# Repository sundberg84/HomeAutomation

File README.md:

# Homeautomation Backup! 
My homeautomation stuff backup place :)

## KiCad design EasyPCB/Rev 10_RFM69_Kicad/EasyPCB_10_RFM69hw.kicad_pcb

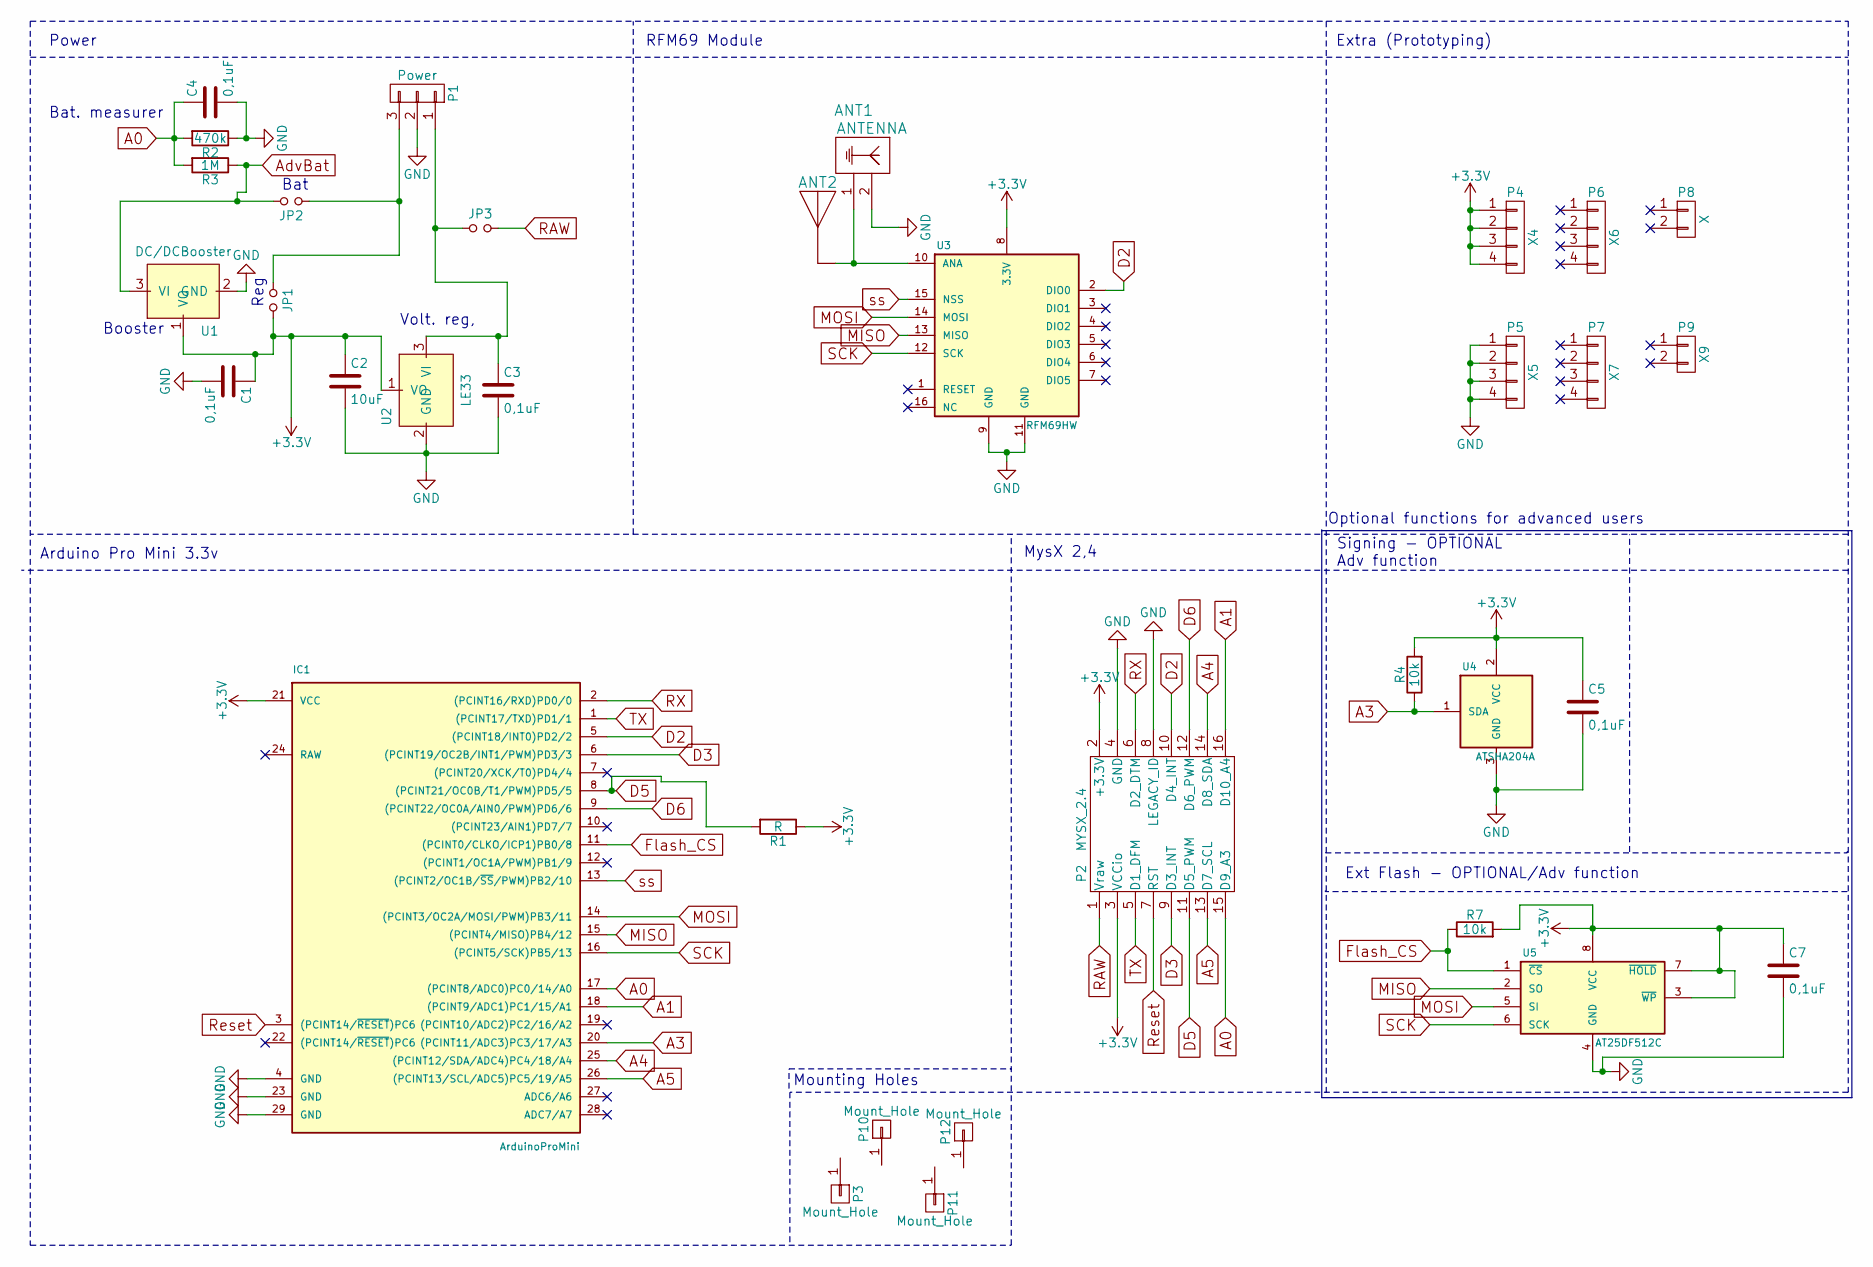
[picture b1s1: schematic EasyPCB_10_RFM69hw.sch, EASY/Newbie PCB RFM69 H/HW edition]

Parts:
ANT1: ANTENNA; SMA_EDGE
ANT2: ANTENNA; Pin_Header_Straight_1x01_Pitch2.54mm
C1, C3, C4: 0,1uF; CP_Radial_D5.0mm_P2.50mm
C2: 10uF; CP_Radial_D5.0mm_P2.50mm
C5, C7: 0,1uF; C_0805_HandSoldering
IC1: ArduinoProMini; pro_mini
JP1: REG; Pin_Header_Straight_1x02_Pitch2.54mm
JP2: BAT; Pin_Header_Straight_1x02_Pitch2.54mm
JP3: RAW; Pin_Header_Straight_1x02_Pitch2.54mm
P1: Power; 3_block_Screw_Terminal
P2: MYSX_2.4
P3, P10, P11, P12: Mount_Hole; MountingHole_2.5mm
P4: X4; Pin_Header_Straight_1x04_Pitch2.54mm
P5: X5; Pin_Header_Straight_1x04_Pitch2.54mm
P6: X6; Pin_Header_Straight_1x04_Pitch2.54mm
P7: X7; Pin_Header_Straight_1x04_Pitch2.54mm
P8: X; Pin_Header_Straight_1x02_Pitch2.54mm
P9: X9; Pin_Header_Straight_1x02_Pitch2.54mm
R1: R; R_Axial_DIN0207_L6.3mm_D2.5mm_P10.16mm_Horizontal
R2: 470k; R_Axial_DIN0207_L6.3mm_D2.5mm_P7.62mm_Horizontal
R3: 1M; R_Axial_DIN0207_L6.3mm_D2.5mm_P7.62mm_Horizontal
R4, R7: 10k; R_0805_HandSoldering
U1: DC/DCBooster; Pin_Header_Straight_1x03_Pitch2.54mm
U2: LE33; TO-92_LE33_Andreas
U3: RFM69HW; RFM69HW_SMD_ThroughHole_Handsoldering
U4: ATSHA204A; SOT-23_Handsoldering
U5: AT25DF512C; SOIC-8_3.9x4.9mm_Pitch1.27mm

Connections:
+3V3: C1.1, C2.1, C5.1, C7.1, IC1.21 (VCC), JP1.2, P2.2 (+3.3V), P2.3 (VCCio), P4.1, P4.2, P4.3, P4.4, R1.1, R4.2, R7.2, U1.1 (VO), U2.1 (VO), U3.8 (3.3V), U4.2 (VCC), U5.3 (~WP), U5.7 (~HOLD), U5.8 (VCC)
A0: C4.1, IC1.17 ((PCINT8/ADC0)PC0/14/A0), P2.15 (D9_A3), R2.2, R3.2
A1: IC1.18 ((PCINT9/ADC1)PC1/15/A1), P2.16 (D10_A4)
A3: IC1.20 ((PCINT11/ADC3)PC3/17/A3), R4.1, U4.1 (SDA)
A4: IC1.25 ((PCINT12/SDA/ADC4)PC4/18/A4), P2.14 (D8_SDA)
A5: IC1.26 ((PCINT13/SCL/ADC5)PC5/19/A5), P2.13 (D7_SCL)
AdvBat: JP2.2, R3.1, U1.3 (VI)
D2: IC1.5 ((PCINT18/INT0)PD2/2), P2.10 (D4_INT), U3.2 (DIO0)
D3: IC1.6 ((PCINT19/OC2B/INT1/PWM)PD3/3), P2.9 (D3_INT)
D5: IC1.8 ((PCINT21/OC0B/T1/PWM)PD5/5), P2.11 (D5_PWM), R1.2
D6: IC1.9 ((PCINT22/OC0A/AIN0/PWM)PD6/6), P2.12 (D6_PWM)
Flash_CS: IC1.11 ((PCINT0/CLKO/ICP1)PB0/8), R7.1, U5.1 (~CS)
GND: ANT1.2, C1.2, C2.2, C3.2, C4.2, C5.2, C7.2, IC1.4 (GND), IC1.23 (GND), IC1.29 (GND), P1.2, P2.4 (GND), P2.8 (LEGACY_ID), P5.1, P5.2, P5.3, P5.4, R2.1, U1.2 (GND), U2.2 (GND), U3.9 (GND), U3.11 (GND), U4.3 (GND), U5.4 (GND)
MISO: IC1.15 ((PCINT4/MISO)PB4/12), U3.13 (MISO), U5.2 (SO)
MOSI: IC1.14 ((PCINT3/OC2A/MOSI/PWM)PB3/11), U3.14 (MOSI), U5.5 (SI)
unnamed: ANT1.1, ANT2.1, U3.10 (ANA)
unnamed: C3.1, JP3.1, P1.1, U2.3 (VI)
unnamed: JP1.1, JP2.1, P1.3
RAW: JP3.2, P2.1 (Vraw)
RX: IC1.2 ((PCINT16/RXD)PD0/0), P2.6 (D2_DTM)
Reset: IC1.3 ((PCINT14/~RESET~)PC6), P2.7 (RST)
SCK: IC1.16 ((PCINT5/SCK)PB5/13), U3.12 (SCK), U5.6 (SCK)
TX: IC1.1 ((PCINT17/TXD)PD1/1), P2.5 (D1_DFM)
ss: IC1.13 ((PCINT2/OC1B/~SS~/PWM)PB2/10), U3.15 (NSS)

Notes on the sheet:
Reg
Bat
Power
Bat. measurer
Booster
Volt. reg,
MysX 2,4
Extra (Prototyping)
RFM69 Module
Arduino Pro Mini 3.3v
Signing - OPTIONAL Adv function
Ext Flash - OPTIONAL/Adv function
Optional functions for advanced users
Mounting Holes

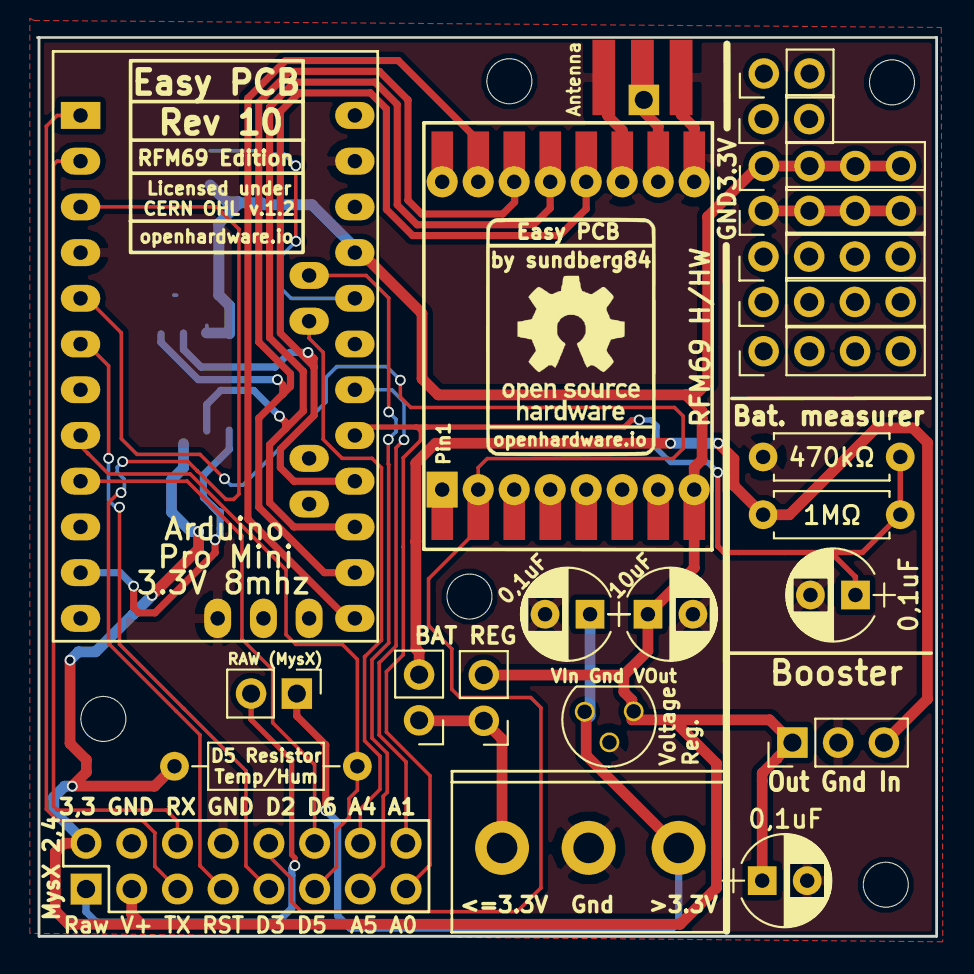
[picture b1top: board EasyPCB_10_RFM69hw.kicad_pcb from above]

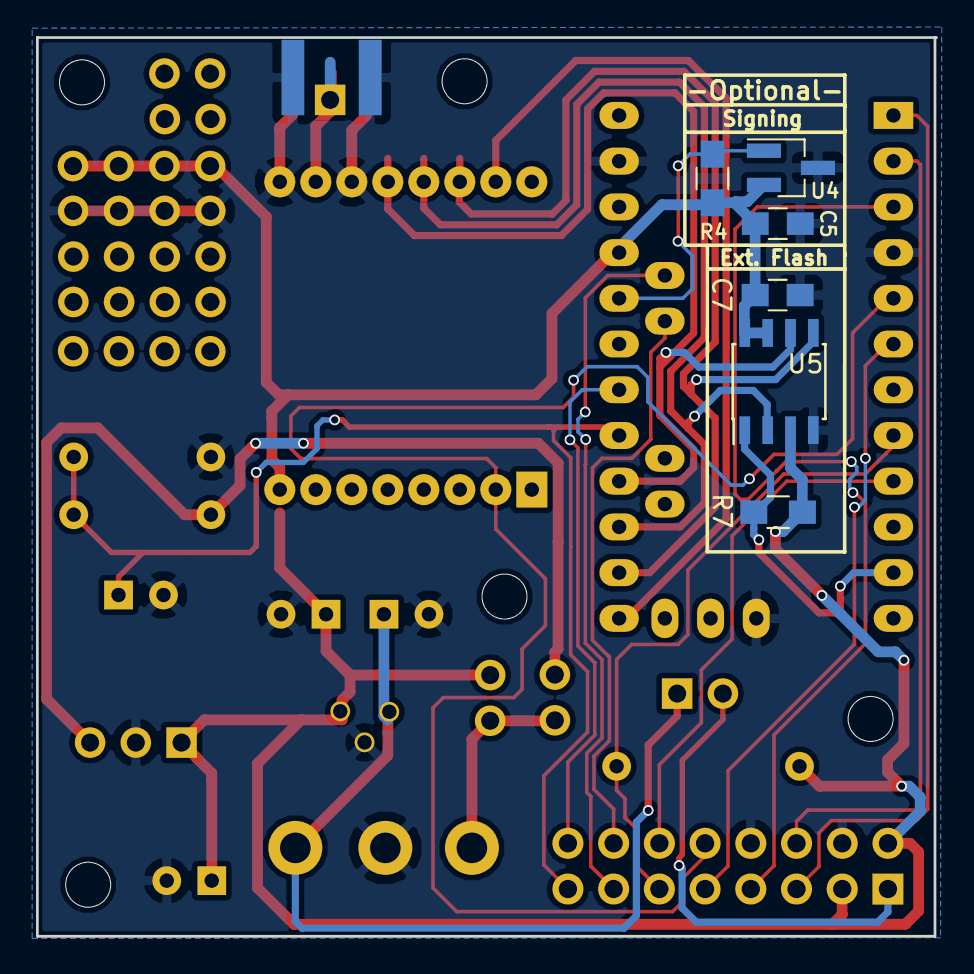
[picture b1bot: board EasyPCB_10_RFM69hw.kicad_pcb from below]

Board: 2 copper layers, 50.0 x 49.9 mm, 36 parts (6 on the bottom side), 24 nets.

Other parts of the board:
P3#2, P3#3: Mount_Hole; MountingHole_2.5mm
P7#2: X7; Pin_Header_Straight_1x04_Pitch2.54mm

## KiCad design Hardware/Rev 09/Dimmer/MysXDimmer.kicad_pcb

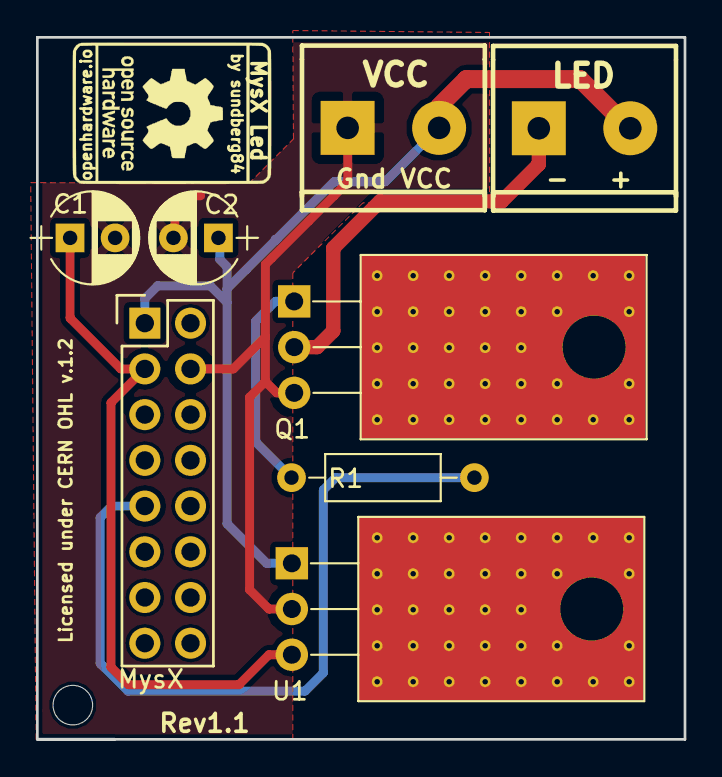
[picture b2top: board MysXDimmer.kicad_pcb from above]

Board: 2 copper layers, 36.0 x 39.0 mm, 8 parts (0 on the bottom side), 6 nets.

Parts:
C1, C2: CP1; CP_Radial_D5.0mm_P2.50mm
LED: CONN_LED; mors_2p
MysX: CONN_02X06; MYSX_2.4
Q1: IRLZ44; TO-220-3_w_heatsink
R1: R; R_Axial_DIN0207_L6.3mm_D2.5mm_P10.16mm_Horizontal
U1: LM2940/LM2940C; TO-220-3_w_heatsink
VCC: CONN_12vDC; mors_2p

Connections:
12v: C2.1, LED.2, MysX.1, U1.1, VCC.2
12vLed: LED.1, Q1.2
+5V: C1.1, MysX.3, U1.3
GND: C1.2, C2.2, MysX.4, Q1.2, Q1.3, Q1.4, U1.2, VCC.1
LED1: MysX.9, R1.2
unnamed: Q1.1, R1.1

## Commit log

2016-09-13 :boom::camel: Added .gitattributes & .gitignore files
2016-09-13 Nya filer
    Nya sketcher
2017-01-10 Energimeter
2017-01-17 NorrHum
2017-02-05 Somethings
2017-02-05 en till
2017-02-06 Removed resend 0 and trigger=!oldtrigger
2017-02-20 Div från kallaren
2017-02-21 Create FirstCommunication1245
2017-02-21 Change format txt
2017-02-21 SerialTest för gw
2017-03-01 Create ComNibeHardwareSerial
2017-04-21 UV Changes
    UV CHanges
2017-08-12 New stuff
2017-08-31 Create Log24hRFM
2017-08-31 Rename Log24hRFM to Log24hRFM.txt
2017-08-31 Rename Log24hRFM.txt to Logs/Log24hRFM.txt
2017-08-31 Rename Log24hNRF.txt to Log24h_NRF_REG.txt
2017-08-31 Rename Log24hRFM.txt to Log24hRFM_REG.txt
2017-08-31 Rename Log24hRFM_REG.txt to Log24h_RFM_REG.txt
2017-08-31 Create LOG24h_RFM_BAT
2017-09-16 New files!
2017-10-25 Some new Files and updates.
2017-11-23 New structure
2017-11-23 Openlogger added to project.
2018-01-07 Update BatteryMeasurer.ino
    If debug defined
2018-02-17 Added MysX Template
2018-02-17 Image
    Image
2018-02-17 Added mounting holes
    M Hole
2018-02-17 Image
2018-03-07 Nodes
2018-03-07 RadioTester
2018-03-08 New File
2018-03-16 TimeAwareSensor Mys 2
2018-04-19 MysXDimmer
2018-06-05 EasyPCB Revision 10 update
    EasyPCB Revision 10 update
2018-06-05 Uploaded Rev 10 Gerber
2018-06-05 Rename MysX template EasyPCB/MysX Template EasyPCB Rev10-B.Cu.gbr to MysX template EasyPCB/Gerber/MysX Template EasyPCB Rev10-B.Cu.gbr
2018-06-05 Rename MysX template EasyPCB/MysX Template EasyPCB Rev10-B.Mask.gbr to MysX template EasyPCB/Gerber/MysX Template EasyPCB Rev10-B.Mask.gbr
2018-06-05 Rename MysX template EasyPCB/MysX Template EasyPCB Rev10-B.SilkS.gbr to MysX template EasyPCB/Gerber/MysX Template EasyPCB Rev10-B.SilkS.gbr
2018-06-05 Rename MysX template EasyPCB/MysX Template EasyPCB Rev10-Edge.Cuts.gbr to MysX template EasyPCB/Gerber/MysX Template EasyPCB Rev10-Edge.Cuts.gbr
2018-06-05 Rename MysX template EasyPCB/MysX Template EasyPCB Rev10-F.Cu.gbr to MysX template EasyPCB/Gerber/MysX Template EasyPCB Rev10-F.Cu.gbr
2018-06-05 Rename MysX template EasyPCB/MysX Template EasyPCB Rev10-F.Mask.gbr to MysX template EasyPCB/Gerber/MysX Template EasyPCB Rev10-F.Mask.gbr
2018-06-05 Rename MysX template EasyPCB/MysX Template EasyPCB Rev10-F.SilkS.gbr to MysX template EasyPCB/Gerber/MysX Template EasyPCB Rev10-F.SilkS.gbr
2018-06-05 Rename MysX template EasyPCB/MysX Template EasyPCB Rev10-NPTH.drl to MysX template EasyPCB/Gerber/MysX Template EasyPCB Rev10-NPTH.drl
2018-06-05 Rename MysX template EasyPCB/MysX Template EasyPCB Rev10.drl to MysX template EasyPCB/Gerber/MysX Template EasyPCB Rev10.drl
2018-06-06 Från Källardatorn
2019-04-07 Update DoorBellDec1mhz.ino
    Change interrupt from Bool to Int
2020-02-09 Removed things to clean up

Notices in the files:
EasyPCB/Rev 10_RFM69_Kicad/EasyPCB_10_RFM69hw.kicad_pcb:
Licensed under
CERN OHL v.1.2
EasyPCB/Rev 10_RFM69_Kicad/EasyPCB_10_RFM69hw.sch:
License: CERN Open Hardware License
Hardware/Rev 09/Dimmer/MysXDimmer.kicad_pcb:
Licensed under CERN OHL v.1.2
